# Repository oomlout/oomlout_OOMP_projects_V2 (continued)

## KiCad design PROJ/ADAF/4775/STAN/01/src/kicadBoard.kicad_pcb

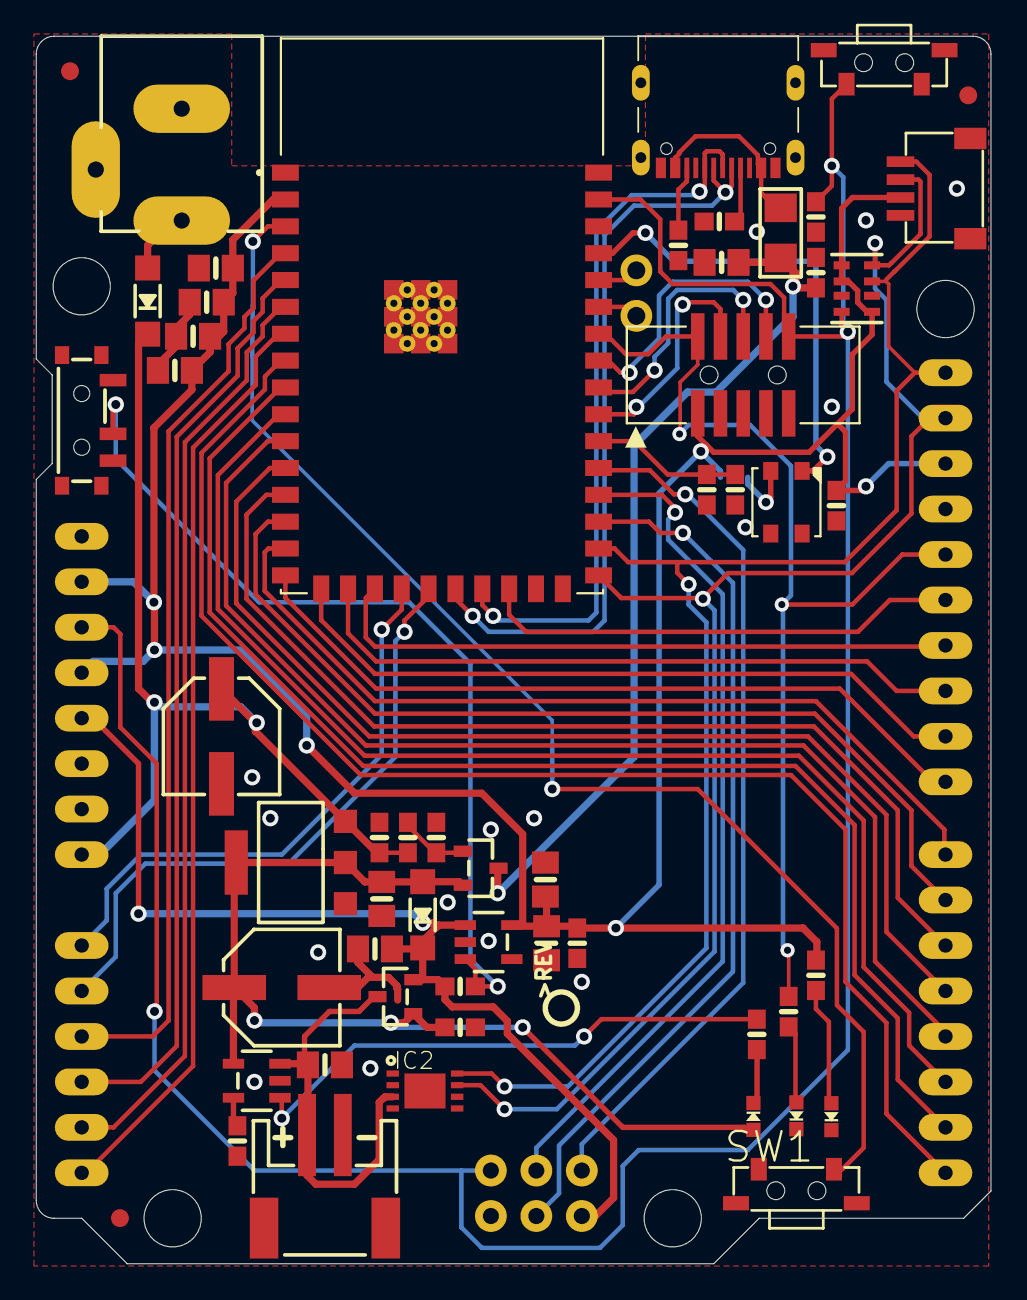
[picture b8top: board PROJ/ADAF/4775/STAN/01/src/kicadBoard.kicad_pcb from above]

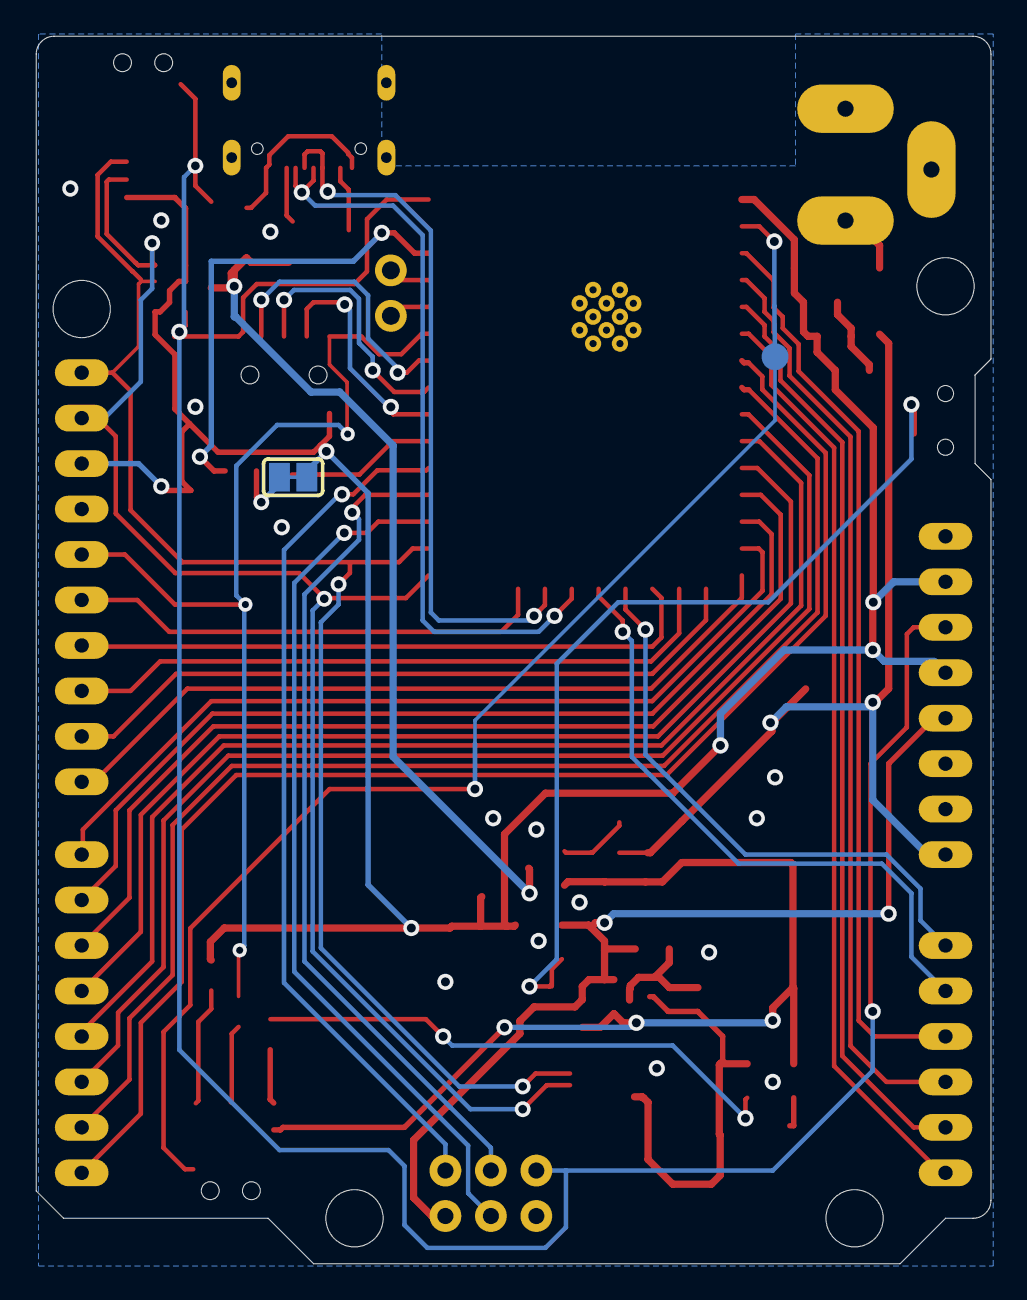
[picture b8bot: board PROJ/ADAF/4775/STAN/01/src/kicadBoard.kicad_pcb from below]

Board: 2 copper layers, 53.3 x 68.6 mm, 70 parts (3 on the bottom side), 55 nets.

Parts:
@HOLE0, @HOLE1, @HOLE2, @HOLE3: (no value)
AD0: 20609; 1X06_OVALWAVE
C1, C3: 10uF; 0805-NO
C2, C5, C12, C15: 0.1uF; 0603-NO
C4, C7, C8, C10, C11, C13, C17, C18: 10µF; 0805-NO
C6, C14: 1uF; 0603-NO
CHG1: ORANGE; CHIPLED_0603_NOOUTLINE
CONN1: STEMMA_I2C_QT; JST_SH4
D1, D4: MBR540; SOD-123
F2: 500mA; 1206
FD1, FD2, FD3: FIDUCIAL_1MM
IC2: LC709203F; WDFN8_3X4_0.65
ICSP0: 3x2 M; 2X03_ROUND_70MIL
IOH0: 20611; 1X10_OVALWAVE
IOL0: 20610; 1X08_OVALWAVE
JP2: UART; 1X02_ROUND
L0: RED; CHIPLED_0603_NOOUTLINE
LED1: WS2812B3535; LED3535
ON0: GREEN; CHIPLED_0603_NOOUTLINE
PC1: 47uF/25V; PANASONIC_D
PC2: 47uF+/6.3V+; PANASONIC_D
POWER0: 20610; 1X08_OVALWAVE
Q1, Q2: DMG3415U-7; SOT23-R
R1: 10K; RESPACK_4X0603
R2, R6, R9: 10K; 0603-NO
R3, R8: 5.1K; 0603-NO
R4: 2.2K; 0603-NO
R12, R15, R16: 100K; 0603-NO
R14: 100k; 0603-NO
R17: 1Meg; 0603-NO
SJ1: SOLDERJUMPER_CLOSEDWIRE
SW1, SW3: RA_TACT; SPST_TACTILE_RA
SW4: SPDT R/A; SPDT_SMT_SSSS811101
TP1: TESTPOINT_ROUND_1.5MM_NO
U1: NCP1117ST50T3G; SOT223-R
U2: MCP73831T-2ACI/OT; SOT23-5
U3: ESP32-S2-WROVER; MODULE_ESP32-S2-WROVER
U4: AP2112(3.3V); SOT23-5
U$15: PCBFEAT-REV-040
U$52: ESP32S2_TOP
U$53: ESP32S2_BOT
X1: JSTPH; JSTPH2_BATT
X2: 4u20317; 2X05_1.27MM_BOX_POSTS
X4: USB C; USB_C_CUSB31-CFM2AX-01-X
X5: 2.1mm; DCJACK_2MM_PTH

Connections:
3.3V: C2.1, C4.1, C5.1, C7.1, C10.1, C13.1, C17.1, C18.1, CONN1.2, IOH0.3, POWER0.2, POWER0.4, R1.1, R1.5, R1.6, R6.2, SJ1.2, U3.2, U4.5, X2.1
+5V: C3.2, CHG1.A, D4.A, PC2.+, Q1.1, Q2.2, R14.2, U1.2, U1.4, U2.4
AD0: AD0.1, U3.20
AD1: AD0.2, U3.21
AD2: AD0.3, U3.4
AD3: AD0.4, U3.5
AD4: AD0.5, U3.6
AD5: AD0.6, U3.7
BOOT0: SW1.2, TP1.P$1, U3.3
D5: IOL0.8, U3.8
D6: IOL0.7, U3.9
D7: IOL0.6, U3.10
D8: IOL0.5, U3.11
D9: IOL0.4, U3.12
D10: IOL0.3, U3.13
D11: IOL0.2, U3.14
D12: IOL0.1, U3.15
D13: IOH0.10, U3.16
D14: IOH0.9, U3.17
D15: IOH0.8, U3.18
D16: IOH0.7, U3.19
D21: IOH0.6, U3.24
D+: U3.23, X4.A6, X4.B6
D-: U3.22, X4.A7, X4.B7
EN: R12.1, SW4.B, U4.3
GND: C1.2, C2.2, C3.1, C4.2, C5.2, C6.2, C7.2, C8.2, C10.2, C11.2, C12.2, C13.2, C14.2, C15.2, C17.2, C18.2, CONN1.1, CONN1.MT1, CONN1.MT2, IC2.1, IC2.2, ICSP0.6, IOH0.4, L0.C, LED1.4, ON0.C, PC1.-, PC2.-, POWER0.6, POWER0.7, R3.1, R4.2, R8.1, R14.1, R16.1, R17.1, SW1.1, SW3.1, SW4.C, U1.1, U2.2, U3.1, U3.26, U3.42, U3.43_1, U3.43_2, U3.43_3, U3.43_4, U3.43_5, U3.43_6, U3.43_7, U3.43_8, U3.43_9, U3.43_10, U3.43_11, U3.43_12, U3.43_13, U3.43_14, U3.43_15, U3.43_16, U3.43_17, U3.43_18, U3.43_19, U3.43_20, U3.43_21, U4.2, X1.1, X2.3, X2.5, X2.7, X2.9, X4.A1B12, X4.B1A12, X5.GND, X5.GNDBREAK
IO38_DBLTAP: C6.1, R17.2, U3.32
MISO: ICSP0.1, U3.31
MOSI: ICSP0.4, U3.29
unnamed: L0.A, R9.1
unnamed: Q2.1, R15.1, R16.2
unnamed: ON0.A, R6.1
unnamed: CHG1.C, R2.1
unnamed: LED1.2, SJ1.1
unnamed: R2.2, U2.1
unnamed: R8.2, X4.A5
unnamed: R3.2, X4.B5
unnamed: R4.1, U2.5
unnamed: F2.1, X4.A4B9, X4.B4A9
NEOPIX: LED1.1, U3.39
PWR: D1.A, X5.PWR
RESET: C14.1, ICSP0.5, POWER0.3, R1.8, SW3.2, U3.41, X2.10
RXD0: JP2.2, U3.38
SCK: ICSP0.3, U3.30
SCL: CONN1.4, IC2.8, IOH0.1, R1.3, U3.28
SDA: CONN1.3, IC2.7, IOH0.2, R1.4, U3.27
TCK: U3.33, X2.4
TDI: U3.35, X2.8
TDO: U3.34, X2.6
TMS_D42: IOH0.5, R9.2, U3.36, X2.2
TXD0: JP2.1, U3.37
VBAT: C8.1, IC2.3, Q1.3, U2.3, X1.2
VBUS: C1.1, C15.1, F2.2, Q2.3
VHIGH: C11.1, D4.C, ICSP0.2, POWER0.5, Q1.2, R12.2, U4.1
VIN: C12.1, D1.C, PC1.+, POWER0.8, R15.2, U1.3
